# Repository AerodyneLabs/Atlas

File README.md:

Atlas
=====

mbed Nucleo based high-altitude balloon data logger

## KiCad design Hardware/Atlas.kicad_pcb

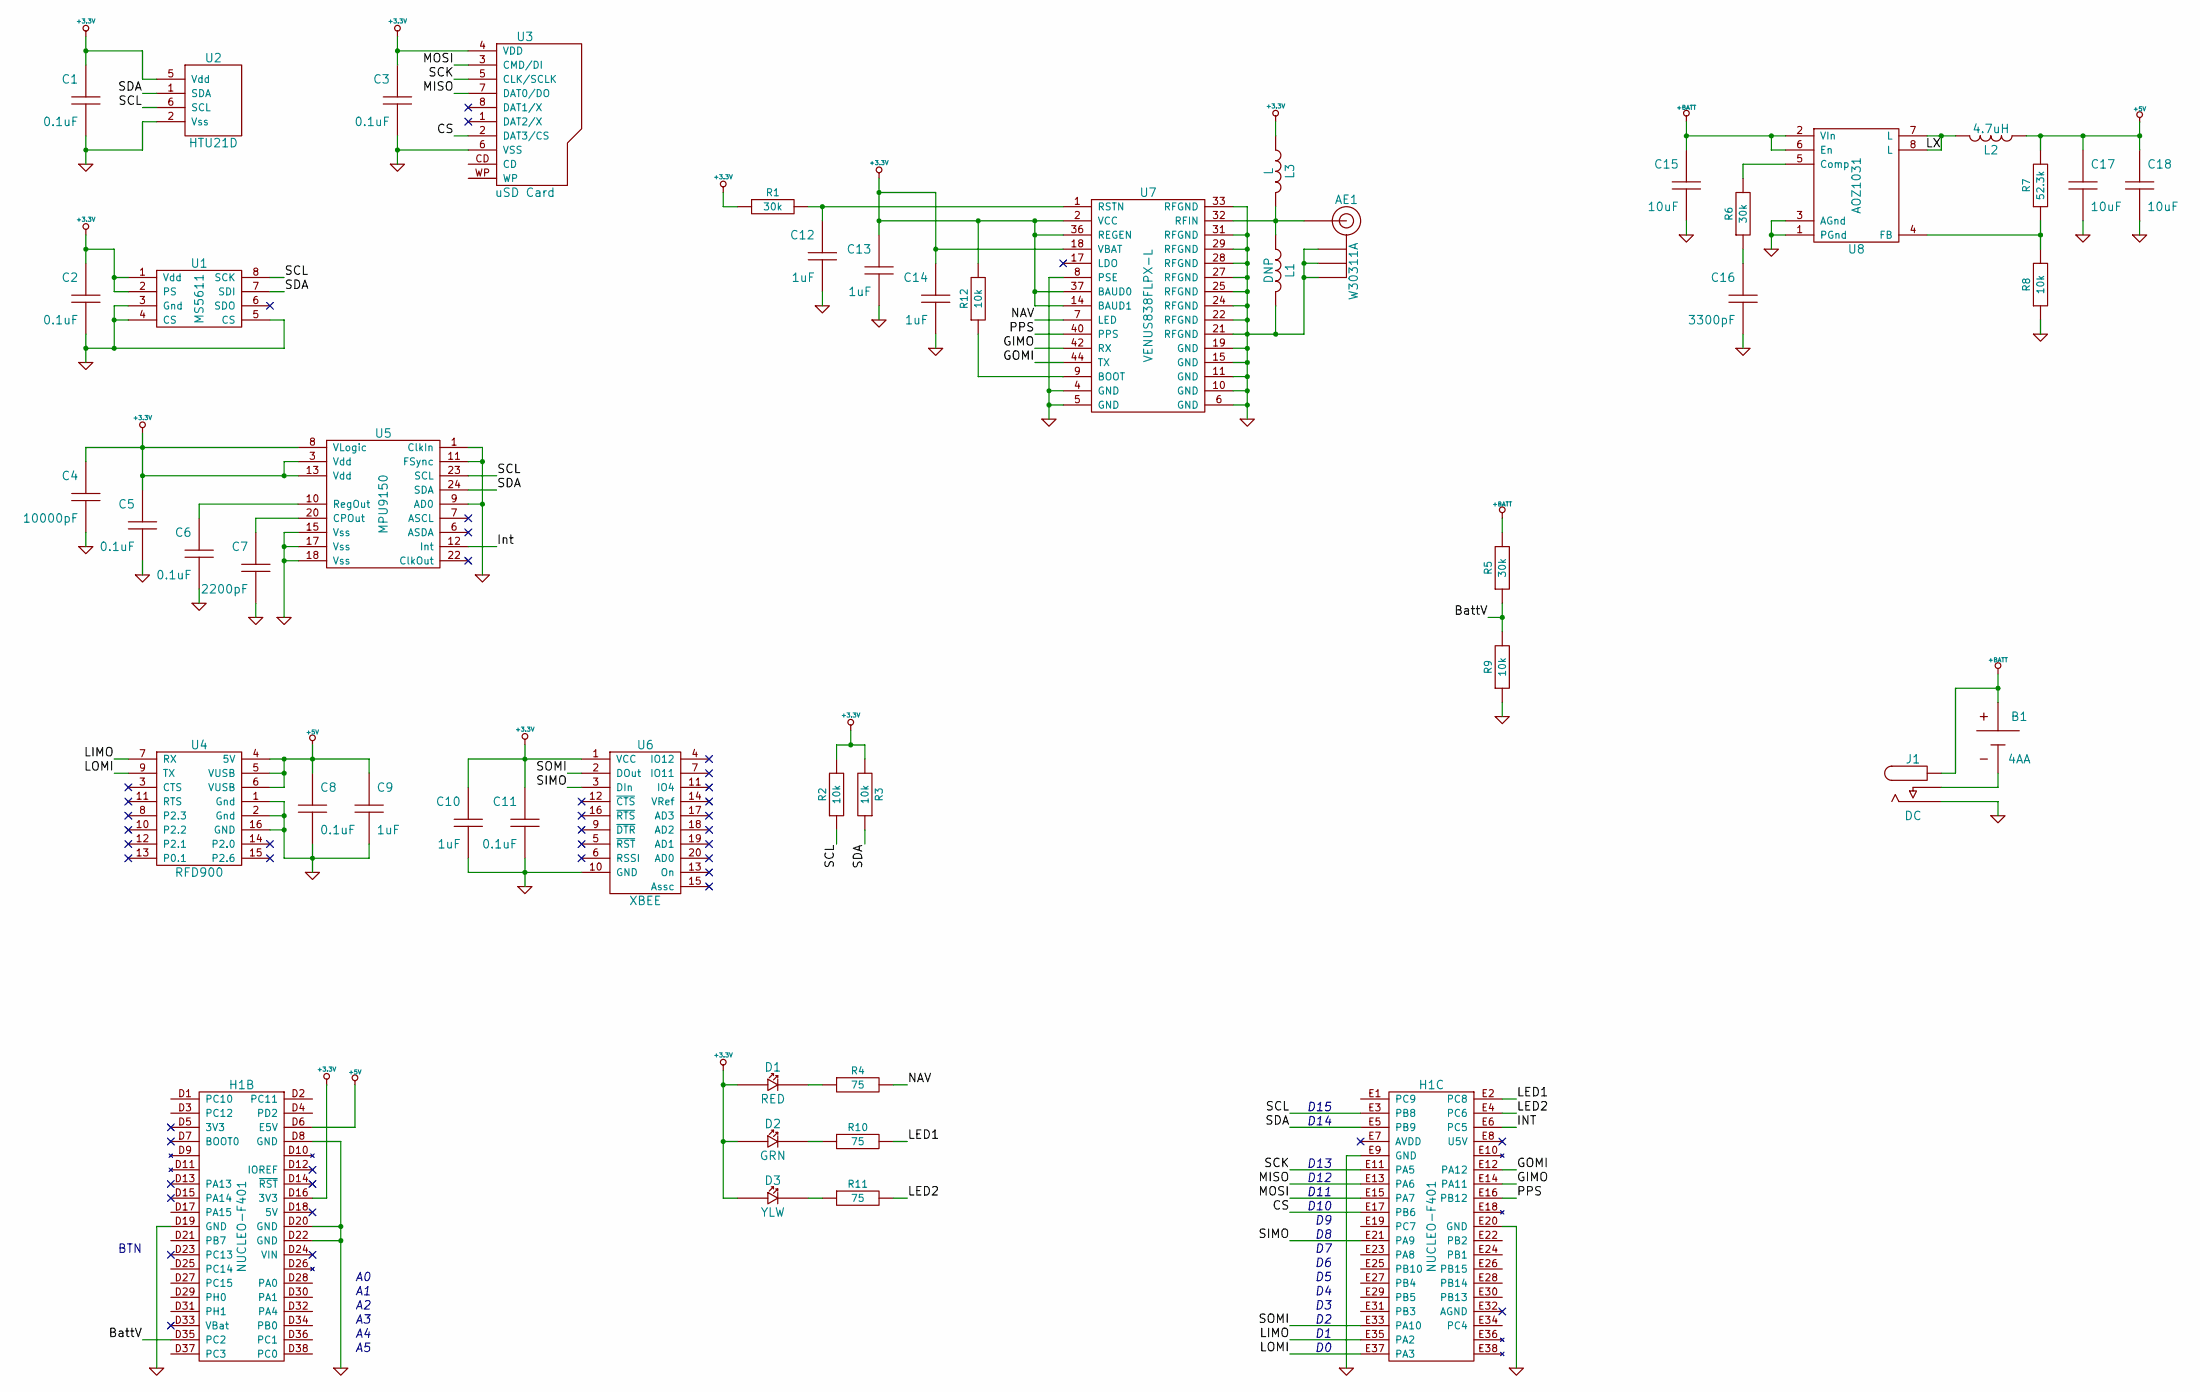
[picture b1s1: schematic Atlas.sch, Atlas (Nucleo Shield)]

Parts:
AE1: W30311A; MFR Part No W3011A
B1: 4AA; MFR Part No 2477
C1, C2, C3, C5, C6, C8, C11: 0.1uF; CAPC1608-N; Voltage 16V; MFR Part No CL10B104KO8NNNC
C4: 10000pF; CAPC1608-N; Voltage 50V; MFR Part No CL10B103KB8NNNC
C7: 2200pF; CAPC1608-N; Voltage 50V; MFR Part No CL10B222KB8SFNC
C9, C10, C12, C13, C14: 1uF; CAPC1608-N; Voltage 10V; MFR Part No CL10B105KP8NNNC
C15, C17, C18: 10uF; CAPC2012-N; Voltage 16V; MFR Part No CL21A106KOFNNNE
C16: 3300pF; CAPC1608-N; Voltage 50V; MFR Part No CL10B332KB8SFNC
D1: RED; LEDC1608-N; Voltage 1.9V; MFR Part No LS Q971-KN-1
D2: GRN; LEDC1608-N; Voltage 2.2V; MFR Part No LG Q971-KN-1
D3: YLW; LEDC1608-N; Voltage 2.0V; MFR Part No LY Q976-P1S2-36
H1: NUCLEO-F401
J1: DC; MFR Part No PJ-202A
L1: DNP; INDC1005-N
L2: 4.7uH; INDC-SRN4018; MFR Part No SRN4018-4R7M
L3: L
R1, R5, R6: 30k; RESC1608-N; Tolerance 5%; MFR Part No MCR03ERTJ303
R2, R3, R8, R9, R12: 10k; RESC1608-N; Tolerance 5%; MFR Part No MCR03ERTJ103
R4, R10, R11: 75; RESC1608-N; Tolerance 5%; MFR Part No MCR03ERTJ750
R7: 52.3k; RESC1608-N; Tolerance 1%; MFR Part No MCR03ERTF5232
U1: MS5611
U2: HTU21D
U3: uSD Card; MFR Part No 101-00303-68
U4: RFD900; MFR Part No PPPC082LJBN-RC
U5: MPU9150
U6: XBEE; MFR Part No NPPN101BFCN-RC
U7: VENUS838FLPX-L
U8: AOZ1031; MFR Part No AOZ1031AI

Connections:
+3.3V: C1.1, C2.1, C3.1, C4.1, C5.1, C10.1, C11.1, C13.1, C14.1, D1.1, D2.1, D3.1, H1.D16 (3V3), L3.2, R1.1, R2.2, R3.2, R12.2, U1.1 (Vdd), U1.2 (PS), U2.5 (Vdd), U3.4 (VDD), U5.3 (Vdd), U5.8 (VLogic), U5.13 (Vdd), U6.1 (VCC), U7.2 (VCC), U7.14 (BAUD1), U7.18 (VBAT), U7.36 (REGEN), U7.37 (BAUD0)
+5V: C8.1, C9.1, C17.1, C18.1, H1.D6 (E5V), L2.2, R7.2, U4.4 (5V), U4.5 (VUSB), U4.6 (VUSB)
+BATT: B1.1, C15.1, J1.1, R5.2, U8.2 (VIn), U8.6 (En)
/BattV: H1.D35 (PC2), R5.1, R9.2
/CS: H1.E17 (PB6), U3.2 (DAT3/CS)
/GIMO: H1.E14 (PA11), U7.42 (RX)
/GOMI: H1.E12 (PA12), U7.44 (TX)
/INT: H1.E6 (PC5), U5.12 (Int)
/LED1: H1.E2 (PC8), R10.2
/LED2: H1.E4 (PC6), R11.2
/LIMO: H1.E35 (PA2), U4.7 (RX)
/LOMI: H1.E37 (PA3), U4.9 (TX)
/LX: L2.1, U8.7 (L), U8.8 (L)
/MISO: H1.E13 (PA6), U3.7 (DAT0/DO)
/MOSI: H1.E15 (PA7), U3.3 (CMD/DI)
/NAV: R4.2, U7.7 (LED)
/PPS: H1.E16 (PB12), U7.40 (PPS)
/SCK: H1.E11 (PA5), U3.5 (CLK/SCLK)
/SCL: H1.E3 (PB8), R2.1, U1.8 (SCK), U2.6 (SCL), U5.23 (SCL)
/SDA: H1.E5 (PB9), R3.1, U1.7 (SDI), U2.1 (SDA), U5.24 (SDA)
/SIMO: H1.E21 (PA9), U6.3 (DIn)
/SOMI: H1.E33 (PA10), U6.2 (DOut)
GND: AE1.S, C1.2, C2.2, C3.2, C4.2, C5.2, C6.2, C7.2, C8.2, C9.2, C10.2, C11.2, C12.2, C13.2, C14.2, C15.2, C16.2, C17.2, C18.2, H1.D8 (GND), H1.D19 (GND), H1.D20 (GND), H1.D22 (GND), H1.E9 (GND), H1.E20 (GND), J1.2, L1.1, R8.1, R9.1, U1.3 (Gnd), U1.4 (CS), U1.5 (CS), U2.2 (Vss), U3.6 (VSS), U4.1 (Gnd), U4.2 (Gnd), U4.16 (GND), U5.1 (ClkIn), U5.9 (AD0), U5.11 (FSync), U5.15 (Vss), U5.17 (Vss), U5.18 (Vss), U6.10 (GND), U7.4 (GND), U7.5 (GND), U7.6 (GND), U7.8 (PSE), U7.10 (GND), U7.11 (GND), U7.15 (GND), U7.19 (GND), U7.21 (RFGND), U7.22 (RFGND), U7.24 (RFGND), U7.25 (RFGND), U7.27 (RFGND), U7.28 (RFGND), U7.29 (RFGND), U7.31 (RFGND), U7.33 (RFGND), U8.1 (PGnd), U8.3 (AGnd)
unnamed: C6.1, U5.10 (RegOut)
unnamed: C7.1, U5.20 (CPOut)
unnamed: C12.1, R1.2, U7.1 (RSTN)
unnamed: R12.1, U7.9 (BOOT)
unnamed: C16.1, R6.1
unnamed: R6.2, U8.5 (Comp)
unnamed: D2.2, R10.1
unnamed: D3.2, R11.1
unnamed: R7.1, R8.2, U8.4 (FB)
unnamed: B1.2, J1.3
unnamed: D1.2, R4.1
unnamed: AE1.P, L1.2, L3.1, U7.32 (RFIN)

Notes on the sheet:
D10
D11
D12
D13
D14
D15
BTN

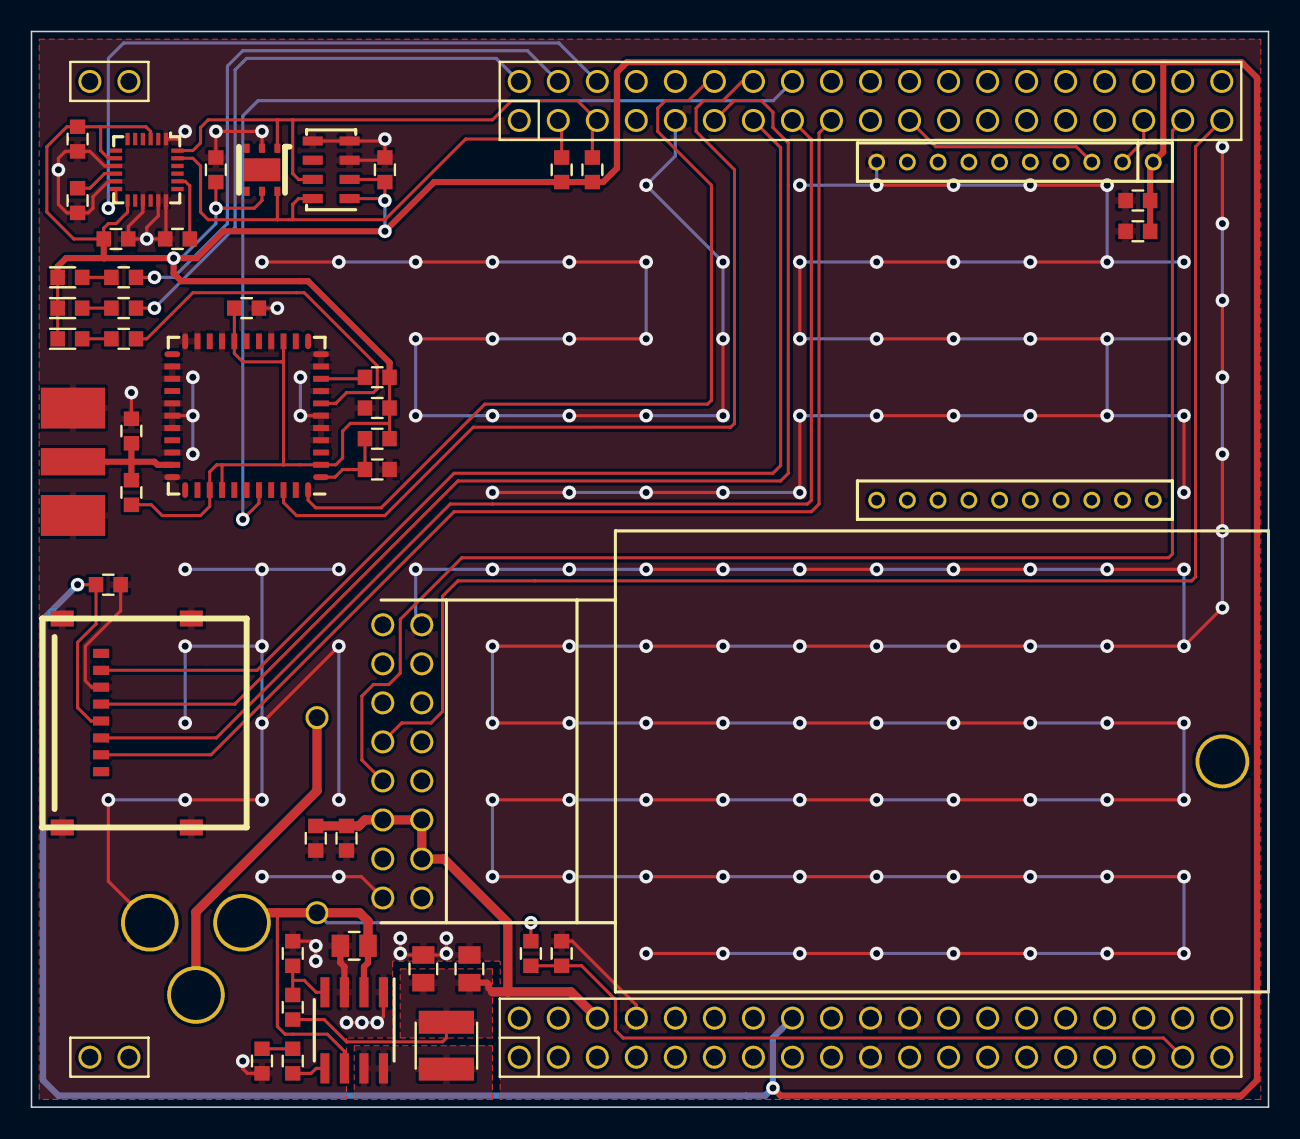
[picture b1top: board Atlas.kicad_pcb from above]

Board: 2 copper layers, 80.5 x 70.0 mm, 48 parts (1 on the bottom side), 35 nets.

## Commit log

2014-05-20 KiCad project configuration
2014-05-21 Add major components to schematic
2014-05-22 Change to bottom shield, remove arduino pins
2014-05-22 Add sensor datasheets
2014-05-22 Add sensor support components
2014-05-22 Wire SD Card
2014-05-23 Layout schematic to reflect board
2014-05-23 Remove XTend because it is stupid
2014-05-23 Add GPS to schematic
2014-05-23 Moar datasheets
2014-05-23 Radio support components
2014-05-24 Even moar datasheet
2014-05-24 Rough netlist, association and layout
2014-05-24 Add 5v regulator and remove before flight switch
2014-05-24 Connect serial peripherals
2014-05-24 Remove split GPS ground
2014-05-25 Majority of layout and routing
2014-05-25 Pre-review layout
2014-05-26 Add LEDs
2014-05-26 Finish PCB
2014-05-28 Update gitignore for gerber outputs
2014-05-28 Add branding to pcb
2014-05-28 DFM changes
2014-05-28 Production files
2014-06-01 Update GPS to support Flash and ROM versions
2014-06-01 Add isolation routing and ground stitching
2014-06-01 Production files for v1.1
2014-06-02 Add mpu9150 register map
2014-06-03 Finish component values and BOM fields
2014-06-21 Add gps command sheet
2014-07-02 Added exemptions for LaTeX files
    Added exemption for addition of LaTeX files for documentation
2014-07-02 Added documentation
    Added documentation folder and start on datasheet/manual for the shield
    itself.
2014-10-18 Switch IMU to QFN footprint
    Fixes #6
2014-10-18 Connect GPS PPS output
    Closes #5
2014-10-30 Switch GPS to SMA antennas port
    Add pull up inductor to support active antenna. Closes #7
